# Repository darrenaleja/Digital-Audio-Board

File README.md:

# Digital Audio Board

## Table of Contents

- [Branch Information](#branch-information)
- [Project Overview](#project-overview)
- [PCB Design Highlights](#pcb-design-highlights)

## Branch Information

- **improvements**: Ongoing updates and enhancements to the initial PCB design are made in this branch. It includes comprehensive revisions in terms of circuit design and layout optimizations.
- **old-iteration**: This branch hosts the original PCB files that were submitted for manufacturing. It represents the first complete design iteration of the audio board.

## Project Overview

I developed this digital audio board to handle and playback digital audio. This repository contains the circuit design, PCB project, datasheets, and detailed documentation needed to understand the digital audio processing workflow implemented.

<p align="center">
  
  <br>
  <em>Improved iteration of PCB design</em>
</p>

This board processes AES3 differential audio signals using a number of components that ensure high-quality audio output:
1. **Receiving AES3 Signal**: Captures AES3 differential audio known for its high reliability and quality in professional audio transmission.
2. **Signal Buffering**: Utilizes a THS4522 buffer op-amp to maintain signal integrity as it feeds into the decoding stage.
3. **Digital Audio Decoding**: The CS8416 digital audio interface receiver decodes the buffered AES3 signal into an I2S digital audio format, supporting various digital audio formats with flexible interfacing.
4. **Microcontroller Processing**: A Raspberry Pi Pico microcontroller converts the I2S signal into a PWM output suitable for driving a speaker and manages I2C control signals for dynamic decoder control.
5. **Audio Output**: Outputs audio through a speaker using the PWM signal generated by the Raspberry Pi Pico.
6. **Signal Passing**: Outputs a single-ended signal from the CS8416 back into the THS4522 for onward transmission, enhancing system flexibility.

<p align="center">
  
  <br>
  <em>Block Diagram of Digital Audio Board</em>
</p>

## PCB Design Highlights

- **Decoupling and Bulk Capacitors**: Incorporates 100nF ceramic decoupling capacitors near IC pins to eliminate high-frequency noise and 10uF aluminum electrolytic capacitors to stabilize supply voltage, critical for high-gain op-amp operations.
- **Symmetry and DNF Resistors**: Features a symmetrical op-amp layout to equalize signal path lengths, reducing phase shifts and susceptibility to EMI.
- **Power and Ground Plane**: Uses continuous planes to reduce impedance and stabilize a low-noise environment, with  cutouts under the op-amp to prevent unwanted capacitance effects.
- **Differential Pair Traces**: Aligns traces meticulously for differential signals to maintain signal integrity and minimize phase errors and external noise susceptibility.

<p align="center">
  
  <br>
  <em>Manufactured PCB of initial design</em>
</p>

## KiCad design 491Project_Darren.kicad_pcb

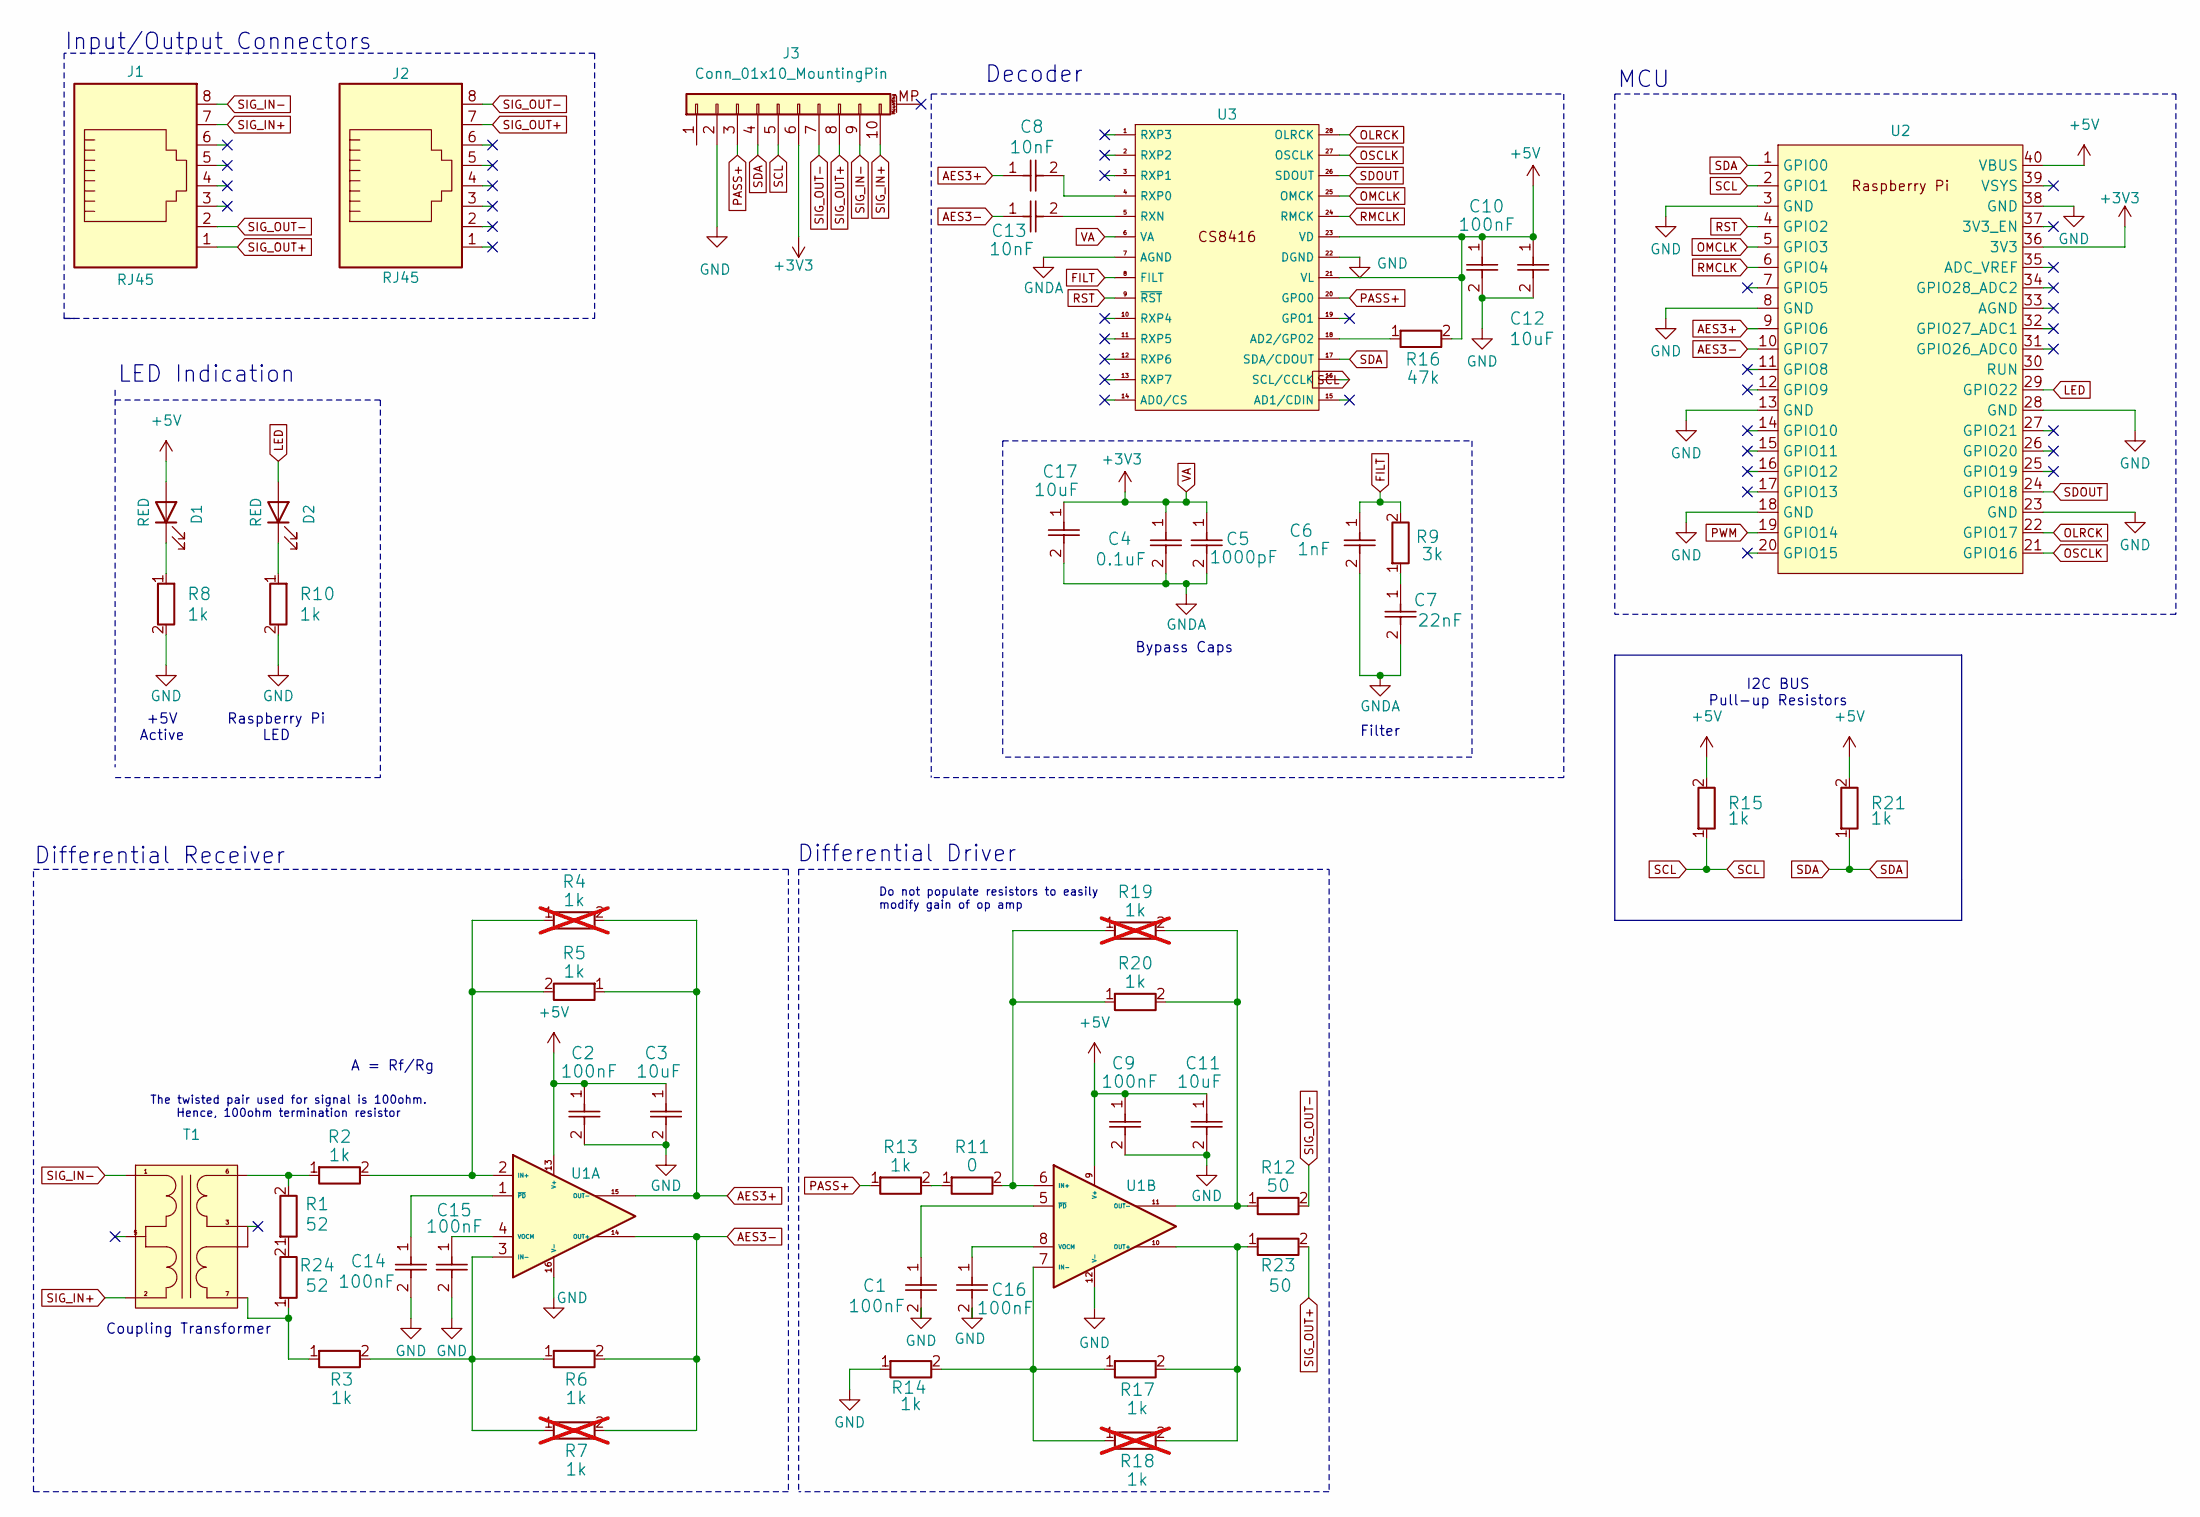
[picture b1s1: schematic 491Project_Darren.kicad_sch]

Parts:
C1, C2, C9, C10, C14, C15, C16: 100nF; C_0805_2012Metric_Pad1.18x1.45mm_HandSolder
C3, C11, C12, C17: 10uF; CAP_ALUM
C4: 0.1uF; C_0805_2012Metric_Pad1.18x1.45mm_HandSolder
C5: 1000pF; C_0805_2012Metric_Pad1.18x1.45mm_HandSolder
C6: 1nF; C_0805_2012Metric_Pad1.18x1.45mm_HandSolder
C7: 22nF; C_0805_2012Metric_Pad1.18x1.45mm_HandSolder
C8, C13: 10nF; C_0805_2012Metric_Pad1.18x1.45mm_HandSolder
D1, D2: RED; LED_D3.0mm
J1, J2: RJ45; RJ45_Conn
J3: Conn_01x10_MountingPin; PinHeader_1x10_P2.54mm_Vertical
R1, R24: 52; C_0805_2012Metric_Pad1.18x1.45mm_HandSolder
R2, R3, R5, R6, R8, R10, R13, R14, R15, R17, R20, R21: 1k; C_0805_2012Metric_Pad1.18x1.45mm_HandSolder
R4, R7, R18, R19: 1k; C_0805_2012Metric_Pad1.18x1.45mm_HandSolder; not fitted
R9: 3k; C_0805_2012Metric_Pad1.18x1.45mm_HandSolder
R11: 0; C_0805_2012Metric_Pad1.18x1.45mm_HandSolder
R12, R23: 50; C_0805_2012Metric_Pad1.18x1.45mm_HandSolder
R16: 47k; C_0805_2012Metric_Pad1.18x1.45mm_HandSolder
T1: SM453230-181N7Y
U1: TSSOP-16_4.4x5mm_P0.65mm
U2: Pico W
U3: SOIC-28W_7.5x17.9mm_P1.27mm

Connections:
+5V: C2.1, C3.1, C9.1, C10.1, C11.1, C12.1, D1.2 (A), R15.2, R16.2, R21.2, U1.9 (V+), U1.13 (V+), U2.40 (VBUS), U3.21 (VL), U3.23 (VD)
AES3+: C8.1, R4.2, R5.1, U1.15 (OUT-), U2.9 (GPIO6)
AES3-: C13.1, R6.2, R7.2, U1.14 (OUT+), U2.10 (GPIO7)
FILT: C6.1, R9.2, U3.8 (FILT)
GND: C1.2, C2.2, C3.2, C9.2, C10.2, C11.2, C12.2, C14.2, C15.2, C16.2, J3.2, R8.2, R10.2, R14.1, U1.12 (V-), U1.16 (V-), U2.3 (GND), U2.8 (GND), U2.13 (GND), U2.18 (GND), U2.23 (GND), U2.28 (GND), U2.38 (GND), U3.22 (DGND)
GNDA: C4.2, C5.2, C6.2, C7.2, C17.2, U3.7 (AGND)
LED: D2.2 (A), U2.29 (GPIO22)
unnamed: C7.1, R9.1
unnamed: D1.1 (K), R8.1
unnamed: D2.1 (K), R10.1
unnamed: R1.1, R24.2
unnamed: R1.2, R2.1, T1.6
unnamed: R11.1, R13.2
unnamed: R3.1, R24.1, T1.7
unnamed: R2.2, R4.1, R5.2, U1.2 (IN+)
unnamed: R3.2, R6.1, R7.1, U1.3 (IN-)
unnamed: C15.1, U1.4 (VOCM)
unnamed: C14.1, U1.1 (~PD)
unnamed: R11.2, R19.1, R20.1, U1.6 (IN+)
unnamed: R14.2, R17.1, R18.1, U1.7 (IN-)
unnamed: R17.2, R18.2, R23.1, U1.10 (OUT+)
unnamed: R12.1, R19.2, R20.2, U1.11 (OUT-)
unnamed: C16.1, U1.8 (VOCM)
unnamed: C1.1, U1.5 (~PD)
unnamed: R16.1, U3.18 (AD2/GPO2)
unnamed: C13.2, U3.5 (RXN)
unnamed: C8.2, U3.4 (RXP0)
OLRCK: U2.22 (GPIO17), U3.28 (OLRCK)
OMCLK: U2.5 (GPIO3), U3.25 (OMCK)
OSCLK: U2.21 (GPIO16), U3.27 (OSCLK)
PASS+: J3.3, R13.1, U3.20 (GPO0)
PWM: U2.19 (GPIO14)
RMCLK: U2.6 (GPIO4), U3.24 (RMCK)
RST: U2.4 (GPIO2), U3.9 (~RST)
SCL: J3.5, R15.1, U2.2 (GPIO1), U3.16 (SCL/CCLK)
SDA: J3.4, R21.1, U2.1 (GPIO0), U3.17 (SDA/CDOUT)
SDOUT: U2.24 (GPIO18), U3.26 (SDOUT)
SIG_IN+: J1.7, J3.10, T1.2
SIG_IN-: J1.8, J3.9, T1.1
SIG_OUT+: J1.1, J2.7, J3.8, R23.2
SIG_OUT-: J1.2, J2.8, J3.7, R12.2
VA: C4.1, C5.1, C17.1, J3.6, U2.36 (3V3), U3.6 (VA)

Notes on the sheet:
Differential Receiver
Raspberry Pi LED
Decoder
Differential Driver
Coupling Transformer
The twisted pair used for signal is 100ohm. Hence, 100ohm termination resistor
Input/Output Connectors
+5V Active
Filter
A = Rf/Rg
MCU
I2C BUS Pull-up Resistors
Do not populate resistors to easily modify gain of op amp
LED Indication
Bypass Caps

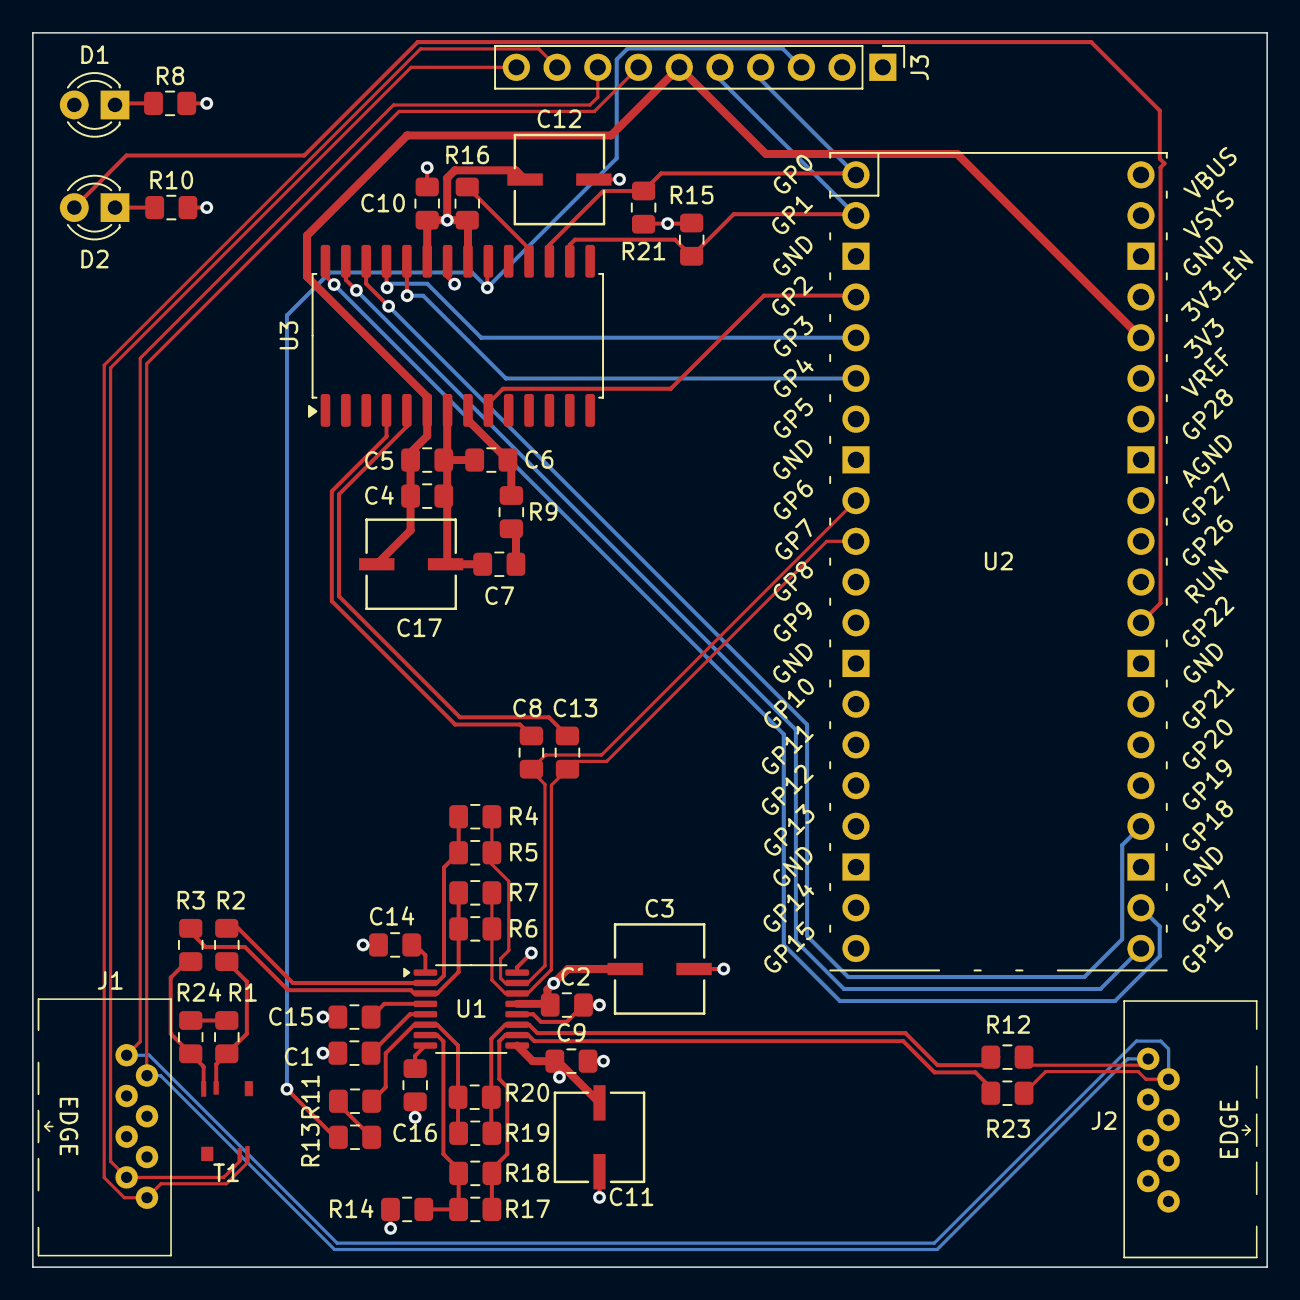
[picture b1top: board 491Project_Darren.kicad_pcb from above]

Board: 4 copper layers, 77.0 x 77.0 mm, 49 parts (0 on the bottom side), 41 nets.

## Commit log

2024-01-26 Update Test Script.py
    Testing each pin voltage
2024-01-26 Added D_Waveform
2024-01-26 Created Folder and Pushed
2024-01-30 Uploaded Pictures
2024-02-06 Uploaded Lab2
2024-02-07 Add files via upload
    Excel file of data recorded during lab one
2024-02-16 Added Textbooks
2024-03-08 Project Initiated
2024-03-09 mar 9
2024-03-09 Group 15
2024-03-14 pi day push
2024-03-15 swag
2024-03-15 Lab Jordan Reviewed kinda
    Pls add pull up resistors!!!!
2024-03-15 Darren
2024-03-15 renaming
2024-03-20 Added Test Pins
2024-03-21 before lab push
2024-03-22 Post lab
    remember to keep differential pairs close together
2024-03-26 Added Power planes, Removed dead copper?
2024-03-31 fix cutouts
2024-04-13 Remove lab file and remove unnecessary files
2024-04-13 Updated footprints to 0603
2024-04-18 changes 0402 footprints to 0805
2024-04-18 Update README.md
    changed order of sections
2024-05-08 updated silkscreen text to 40 mils
2024-05-08 Updated silkscreen
2024-05-08 update images
